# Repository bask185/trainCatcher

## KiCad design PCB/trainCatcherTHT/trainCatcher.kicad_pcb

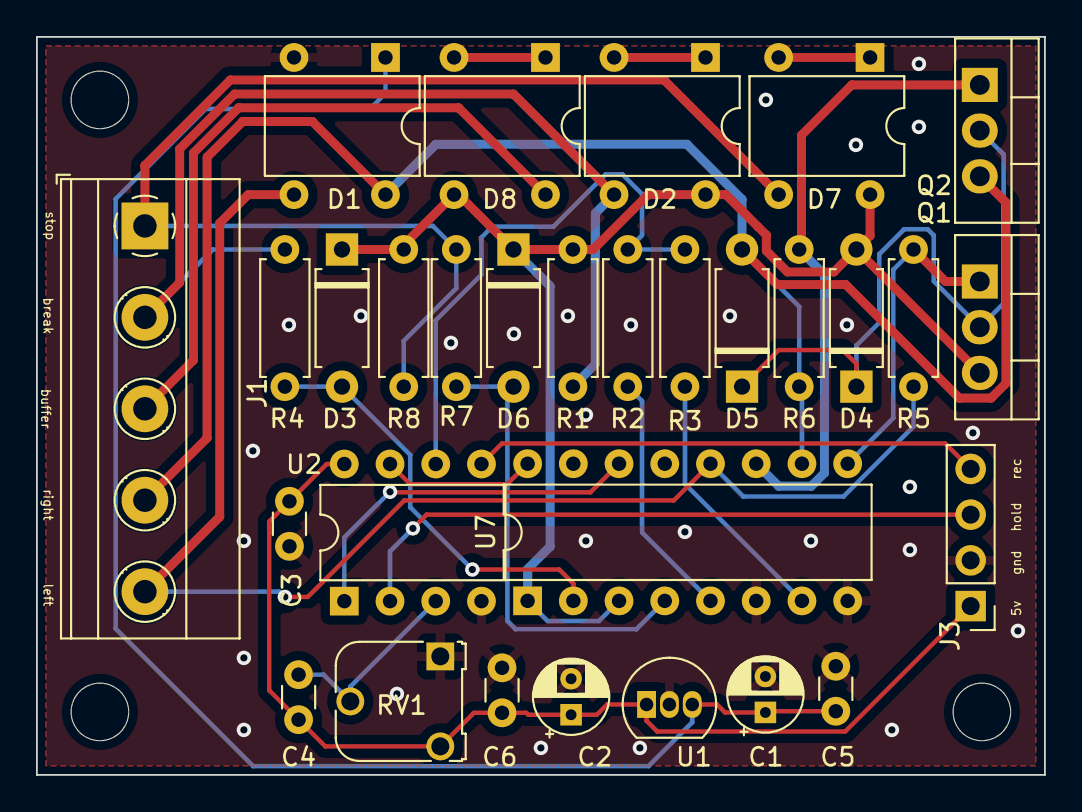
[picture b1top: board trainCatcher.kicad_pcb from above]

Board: 2 copper layers, 56.0 x 41.0 mm, 30 parts (0 on the bottom side), 25 nets.

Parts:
C1, C2: CP; CP_Radial_D4.0mm_P2.00mm
C3, C4, C5, C6: C; C_Disc_D3.0mm_W1.6mm_P2.50mm
D1, D2, D7, D8: D; Diode_Bridge_DIP-4_W7.62mm_P5.08mm
D3, D6: D; D_A-405_P7.62mm_Horizontal
D4, D5: D_Schottky; D_A-405_P7.62mm_Horizontal
J1: break; TerminalBlock_Phoenix_MKDS-1,5-5-5.08_1x05_P5.08mm_Horizont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
J3: Conn_01x04_Male; PinHeader_1x04_P2.54mm_Vertical
Q1, Q2: IRF540N; TO-220-3_Vertical
R1, R8: 4k7; R_Axial_DIN0207_L6.3mm_D2.5mm_P7.62mm_Horizontal
R2, R3: R; R_Axial_DIN0207_L6.3mm_D2.5mm_P7.62mm_Horizontal
R4, R7: 33R; R_Axial_DIN0207_L6.3mm_D2.5mm_P7.62mm_Horizontal
R5, R6: 100k; R_Axial_DIN0207_L6.3mm_D2.5mm_P7.62mm_Horizontal
RV1: R_POT; Potentiometer_Runtron_RM-065_Vertical
U1: MC78L05_TO92; TO-92_Inline
U2: ATtiny13-20PU; DIP-8_W7.62mm
U7: LTV-847; DIP-16_W7.62mm

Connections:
+5V: C2.1, C3.1, C4.2, C6.2, J3.1, RV1.3, U1.1 (VO), U2.8 (VCC)
/PWM: R2.2, R3.1, U2.6 (PB1)
/break: U2.7 (PB2), U7.16
/breakSection: D2.3, J1.2, R1.1, R4.2
/breakSpeed: C4.1, RV1.2, U2.3 (PB4)
/bufferSection: D8.4, J1.3
/hold: J3.3, U2.2 (PB3)
/leftMain: D1.3, J1.5, R5.1, U7.12
/rec: J3.4, U2.5 (PB0)
/rightMain: D1.4, D5.2 (A), J1.4, Q2.3 (S), R6.2, U7.10
/stop: U2.1 (~RESET/PB5), U7.14
/stopTrack: D7.3, J1.1, R7.2, R8.1
GND: C1.2, C2.2, C3.2, C5.1, C6.1, D1.2 (-), J3.2, RV1.1, U1.2 (GND), U2.4 (GND), U7.6, U7.8, U7.13, U7.15
unnamed: C1.1, C5.2, D1.1 (+), U1.3 (VI)
unnamed: D2.1 (+), D2.2 (-)
unnamed: D2.4, D3.1 (K), D4.2 (A), D6.1 (K), D7.4, D8.3, Q1.3 (S), R1.2, R8.2, U7.1, U7.3
unnamed: D4.1 (K), D5.1 (K), Q1.2 (D), Q2.2 (D)
unnamed: D7.1 (+), D7.2 (-)
unnamed: D8.1 (+), D8.2 (-)
unnamed: Q1.1 (G), R5.2, U7.9
unnamed: Q2.1 (G), R6.1, U7.11
unnamed: R2.1, U7.5
unnamed: R3.2, U7.7
unnamed: D3.2 (A), R4.1, U7.2
unnamed: D6.2 (A), R7.1, U7.4

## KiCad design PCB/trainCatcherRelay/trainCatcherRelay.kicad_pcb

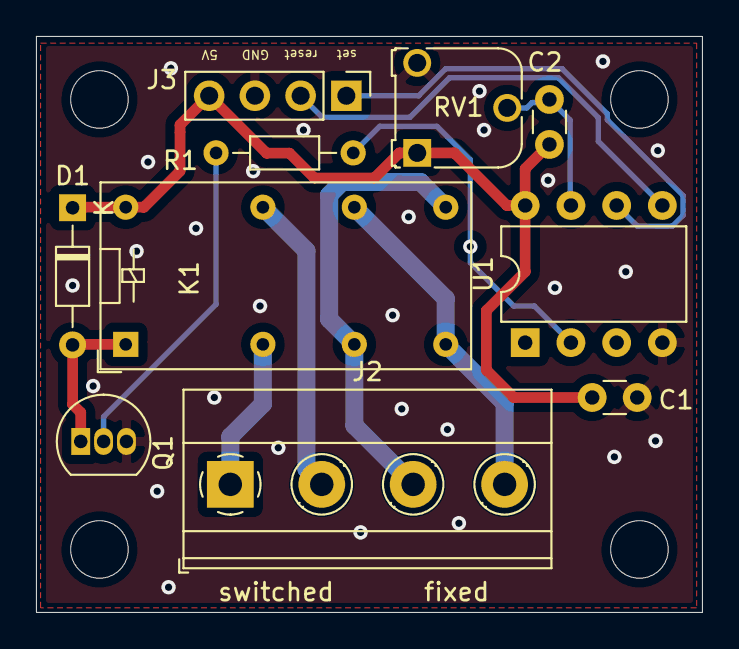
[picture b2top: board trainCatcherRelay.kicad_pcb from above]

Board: 2 copper layers, 37.0 x 32.0 mm, 10 parts (0 on the bottom side), 12 nets.

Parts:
C1, C2: C; C_Disc_D3.0mm_W1.6mm_P2.50mm
D1: D; D_DO-34_SOD68_P7.62mm_Horizontal
J2: tracks; TerminalBlock_Phoenix_MKDS-1,5-4-5.08_1x04_P5.08mm_Horizont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
J3: conn; PinHeader_1x04_P2.54mm_Vertical
K1: G5V-2; Relay_DPDT_Omron_G5V-2
Q1: BC547; TO-92_Inline
R1: R; R_Axial_DIN0204_L3.6mm_D1.6mm_P7.62mm_Horizontal
RV1: R_POT; Potentiometer_Runtron_RM-065_Vertical
U1: ATtiny45-20PU; DIP-8_W7.62mm

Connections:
+5V: C1.1, C2.1, D1.1, J3.4, K1.16, RV1.1, U1.8
/relay: R1.2, U1.2
/reset: J3.2, U1.5
/set: J3.1, U1.6
/timeDelay: C2.2, RV1.2, U1.7
GND: C1.2, J3.3, Q1.3, RV1.3, U1.4
unnamed: D1.2, K1.1, Q1.1
unnamed: J2.1, K1.4
unnamed: J2.2, K1.13
unnamed: J2.3, K1.6, K1.9
unnamed: J2.4, K1.8, K1.11
unnamed: Q1.2, R1.1

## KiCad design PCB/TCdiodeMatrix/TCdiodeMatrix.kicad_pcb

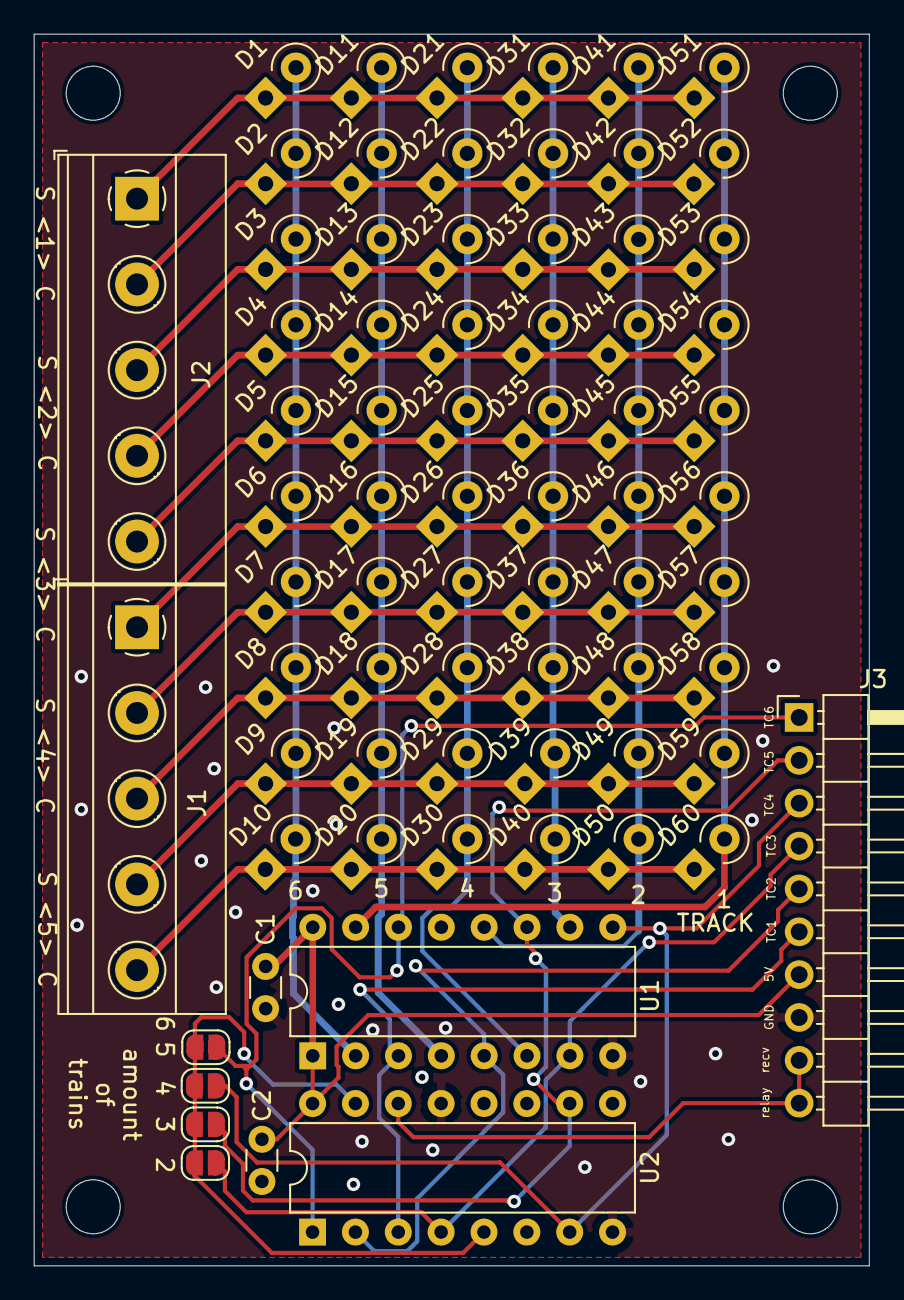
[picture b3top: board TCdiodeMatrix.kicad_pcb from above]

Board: 2 copper layers, 49.5 x 73.0 mm, 71 parts (0 on the bottom side), 26 nets.

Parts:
C1, C2: C; C_Disc_D3.0mm_W1.6mm_P2.50mm
D1, D2, D3, D4, D5, D6, D7, D8, D9, D10, D11, D12, D13, D14, D15, D16, D17, D18, D19, D20, D21, D22, D23, D24, D25, D26, D27, D28, D29, D30, D31, D32, D33, D34, D35, D36, D37, D38, D39, D40, D41, D42, D43, D44, D45, D46, D47, D48, D49, D50, D51, D52, D53, D54, D55, D56, D57, D58, D59, D60: D; D_A-405_P2.54mm_Vertical_KathodeUp
J1, J2: points; TerminalBlock_Phoenix_MKDS-1,5-5-5.08_1x05_P5.08mm_Horizont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
J3: train catchers; PinHeader_1x10_P2.54mm_Horizontal
JP1, JP2, JP3, JP4: ju; SolderJumper-2_P1.3mm_Open_RoundedPad1.0x1.5mm
U1: 4009; DIP-16_W7.62mm
U2: 4017; DIP-16_W7.62mm

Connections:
+5V: C1.1, C2.1, J3.7, U1.1, U1.16, U2.16
/TC1: D51.2, D52.2, D53.2, D54.2, D55.2, D56.2, D57.2, D58.2, D59.2, D60.2, U1.15
/TC2: D41.2, D42.2, D43.2, D44.2, D45.2, D46.2, D47.2, D48.2, D49.2, D50.2, U1.12
/TC3: D31.2, D32.2, D33.2, D34.2, D35.2, D36.2, D37.2, D38.2, D39.2, D40.2, U1.10
/TC4: D21.2, D22.2, D23.2, D24.2, D25.2, D26.2, D27.2, D28.2, D29.2, D30.2, U1.6
/TC5: D11.2, D12.2, D13.2, D14.2, D15.2, D16.2, D17.2, D18.2, D19.2, D20.2, U1.4
/TC6: D1.2, D2.2, D3.2, D4.2, D5.2, D6.2, D7.2, D8.2, D9.2, D10.2, U1.2
/TC_out1: J3.6, U1.3, U2.3
/TC_out2: J3.5, U1.5, U2.2
/TC_out3: J3.4, JP1.1, U1.7, U2.4
/TC_out4: J3.3, JP2.1, U1.9, U2.7
/TC_out5: J3.2, JP3.1, U1.11, U2.10
/TC_out6: J3.1, JP4.1, U1.14, U2.1
/recv: J3.9, J3.10, U2.14
/reset: JP1.2, JP2.2, JP3.2, JP4.2, U2.5, U2.15
GND: C1.2, C2.2, J3.8, U1.8, U2.8, U2.13
unnamed: D1.1, D11.1, D21.1, D31.1, D41.1, D51.1, J2.1
unnamed: D10.1, D20.1, D30.1, D40.1, D50.1, D60.1, J1.5
unnamed: D2.1, D12.1, D22.1, D32.1, D42.1, D52.1, J2.2
unnamed: D3.1, D13.1, D23.1, D33.1, D43.1, D53.1, J2.3
unnamed: D4.1, D14.1, D24.1, D34.1, D44.1, D54.1, J2.4
unnamed: D5.1, D15.1, D25.1, D35.1, D45.1, D55.1, J2.5
unnamed: D6.1, D16.1, D26.1, D36.1, D46.1, D56.1, J1.1
unnamed: D7.1, D17.1, D27.1, D37.1, D47.1, D57.1, J1.2
unnamed: D8.1, D18.1, D28.1, D38.1, D48.1, D58.1, J1.3
unnamed: D9.1, D19.1, D29.1, D39.1, D49.1, D59.1, J1.4

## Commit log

2022-01-31 Project has been made operable for attiny45 chip. The build script works but seems to be fore at85. Upload script does not work at all. Used arduino IDE instead.
    There is a bug that the train will depart in the same direction after being stopped. The hold signal, pwm and detector do seem to work
2022-01-31 changed PCB design of tht trainCatcher
2022-02-01 changed pulse time from 1ms to 500us
2022-04-05 made a change to the new branch so that the polarity check is not done. Also added an 8s delay after the train is accelerated. This delay should fix most problems.
2022-04-05 did some refactoring. Removed some commens and obsolete code
2022-04-05 implemented 8 second delay to awaitTrain after speed reached 100. It would happen that the train catcher would slow down a train just before it's departure.
    In the future it is better to use the current sensor to detect when the train has actually departed driving forward
2022-04-08 added some code to include an automated pause if signal and hold are tied togather. Also temporarily broke the code. I am adding object pointers for the feedback sensor so I can use them in both dire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
2022-04-08 added the 555 pause unit to this repo
2022-04-09 Fixed the PCB to contain the buffer section as well. Also the right rail should now be switched and sensed well. The program has been succesfully altered to issue a 30s unconditional stop if the gold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
2022-04-10 added connection schematic for website
2022-04-11 added more pictures
